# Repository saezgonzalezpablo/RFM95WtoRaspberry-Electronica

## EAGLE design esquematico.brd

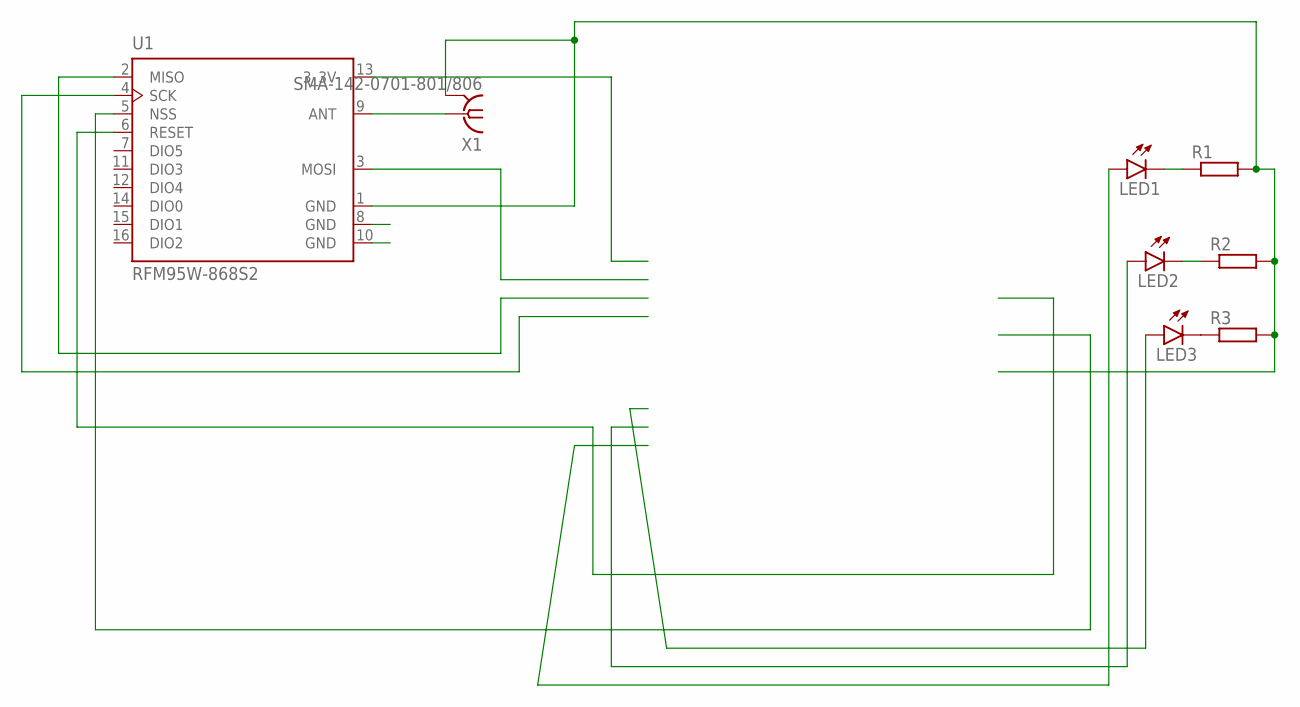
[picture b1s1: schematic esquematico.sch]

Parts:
LED1, LED2, LED3: LED3MM
R1, R2, R3: R-EU_M0805; M0805
U1: RFM95W-868S2; XCVR_RFM95W-868S2
X1: SMA-142-0701-801/806; J502-ND-142-0701-801/806

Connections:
A: U1.8 (GND)
B: U1.10 (GND)
unnamed: U1.9 (ANT), X1.1
unnamed: LED3.K (C), R3.1
unnamed: LED2.K (C), R2.1
unnamed: LED1.K (C), R1.1
unnamed: R1.2, R2.2, R3.2, U1.1 (GND), X1.G@1 (2), X1.G@2 (2), X1.G@3 (2), X1.G@4 (2)

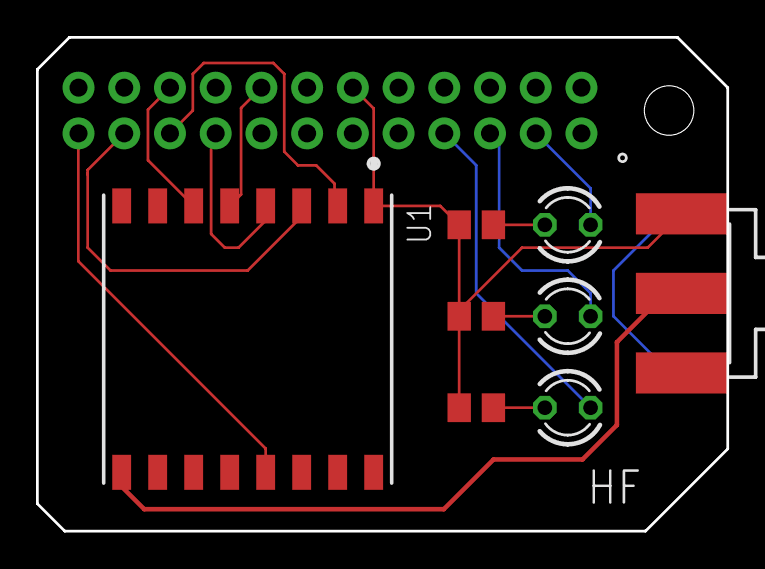
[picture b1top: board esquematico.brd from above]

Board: 2 copper layers, 38.4 x 27.4 mm, 8 parts (0 on the bottom side), 5 nets.

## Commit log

2021-02-23 Proyecto Eagle
